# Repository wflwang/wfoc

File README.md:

# WFOC - 开源低成本高性能FOC电调

WFOC (WFL FOC) 是一款面向开源社区的低成本高性能无刷直流电机 FOC 控制器。项目参考 STM32 FOC 驱动、VESC 开源代码和 SimpleFOC，在国产 CIU32F003x5 (ARM Cortex-M0+) 上实现了完整的电机控制固件。

- 开源地址: https://github.com/wflwang/wfoc.git
- 邮箱: B5106D@Outlook.com

## 项目特点

- **低成本**: 采用国产 MCU (CIU32F003x5) 和 FD6288 栅极驱动，BOM 成本低
- **高性能**: 中断内全定点 Q16.16 运算（无浮点），20kHz PWM 电流环
- **双模式**: 同时支持 FOC 矢量控制和 BLDC 六步换相，可通过 `comm_mode` 配置切换
- **多观测器**: 滑模观测器 (SMO)、MXLEMMA 全阶观测器、MXV_Lambda 补偿、高频注入 (HFI)
- **VESC 风格协议**: 二进制 UART 协议，支持参数读写、实时遥测、高速流式打印
- **开源**: 硬件 (CERN-OHL-S v2) 和软件 (MIT) 全部开源

## 硬件架构

### 核心器件

| 器件 | 型号 | 封装 | 功能 |
|------|------|------|------|
| MCU | CIU32F003x5 | QFN-20 | 32位 ARM Cortex-M0+, 24MHz, 32KB Flash |
| 栅极驱动 | FD6288 | TSSOP-20 | 三相半桥驱动，内置自举二极管 |
| 运算放大器 | XOPA2333 | - | 2通道电流采样放大 |
| MOSFET | N-MOS | TO-252-2 | 3上 + 3下功率开关管 |

### 硬件特性

- **电源输入**: 10-48V DC
- **持续电流**: 20A（峰值 60A）
- **PWM 频率**: 8kHz-20kHz 可调（默认 20kHz）
- **电流采样**: 2路下桥臂电阻采样 (0.005R + 20x 运放)
- **通信接口**: UART (115200~921600) / PPM
- **保护功能**: 过流、过压、欠压、过温保护
- **调试接口**: SWD

### 引脚映射

引脚定义见 [board_config.h](software/config/board_config.h)，摘要：

| 功能 | 引脚 | 说明 |
|------|------|------|
| UART TX/RX | PC0 / PB5 | 串口通信 |
| PWM A 高/低 | PB2 / PB3 | A相上下管 |
| PWM B 高/低 | PC1 / PB7 | B相上下管 |
| PWM C 高/低 | PA1 / PA0 | C相上下管 |
| 电流采样 A/B | PB0 / PB1 | ADC CH0/CH1 |
| 相电压 U/V/W | PA3 / PA4 / PA5 | ADC CH3/CH4/CH5 |
| 母线电压 | PA7 | ADC CH7 |
| 温度 | PA6 | ADC CH6 |
| PPM 输入 | PB4 | TIM2 输入捕获 |

## 软件架构

### 目录结构

```
software/
├── main.c                  # 主程序入口（初始化与主循环）
├── interrupts.c            # 中断服务（ADC1 FOC环 / UART / PPM / SysTick）
├── Makefile                # 编译脚本
│
├── app/                    # 应用层
│   ├── app.c               # 状态机、安全监督、斜坡控制
│   ├── app_uart.c          # UART控制接口（VESC风格协议、实时遥测）
│   ├── app_ppm.c           # PPM脉冲解码
│   └── app_sound.c         # 电机发声
│
├── motor/                  # 电机控制核心
│   ├── mcpwm.c             # PWM后端桥接（duty/current/speed/position）
│   ├── observer.c          # 观测器（SMO / MXLEMMA / HFI + PLL）
│   ├── bldc.c              # BLDC六步换相（多种反电动势检测）
│   └── encoder.c           # 编码器接口
│
├── driver/mcu/             # MCU外设驱动
│   ├── adc.c               # ADC驱动（DMA多通道，偏置校准）
│   ├── pwm.c               # PWM驱动（TIM1三相中心对齐）
│   ├── uart.c              # UART驱动（环形缓冲收发）
│   ├── timer.c             # 定时器（PPM捕获/看门狗）
│   ├── gpio.c              # GPIO配置
│   ├── mcu_init.c          # 系统初始化（时钟/SysTick）
│   └── ciu32f003x.h        # MCU寄存器定义
│
├── conf/                   # 配置系统
│   ├── datatypes.h         # 核心数据类型（motor_state_t / mc_configuration_t）
│   ├── conf_default.c      # 默认参数
│   └── conf_general.c      # 配置管理（持久化接口）
│
├── config/                 # 编译时配置
│   ├── board_config.h      # 板级引脚映射与硬件参数
│   ├── hwconf.h            # 硬件目标选择（make HW=WFoc_V1）
│   └── fw_version.h        # 固件版本与功能开关
│
├── packet/                 # 通信协议
│   └── packet.c            # VESC风格帧封装（CRC16/CCITT）
│
├── startup/                # 启动文件
│   ├── linker.ld           # 链接脚本
│   └── startup_ciu32f003x.s# 启动汇编
│
└── util/                   # 工具库
    └── fixedpoint.c        # 定点数数学库（Q16.16, 三角函数, PI/PID, 陷波滤波）
```

### 数据流

```
ADC1 ISR (20kHz) ──► 电流采样 ──► Clarke ──► 观测器(角度/转速)
                                       │              │
                                       ▼              ▼
                                     Park ──► PI电流环 ──► 逆Park
                                                          │
                                                       SVPWM ──► TIM1 PWM
                                                          │
应用层 (main loop)                                        │
  app_process() ──► mcpwm_set_*() ──► foc_state.iq_set ───┘
  app_uart_process() ──► 遥测发送 ──► UART
```

### 核心功能实现状态

- [x] FOC 矢量控制（Clarke/Park/SVPWM/电流环PI）
- [x] BLDC 六步换相（ADC/比较器/过零检测 + 参数自学习）
- [x] 观测器（SMO / MXLEMMA / HFI + PLL 锁相环）
- [x] 定点数数学库（Q16.16，中断内无浮点）
- [x] VESC 风格 UART 协议（参数读写、固件版本、终端命令）
- [x] 实时遥测（3相电流、3相电压、转速、d/q轴等）
- [x] 高速流式打印（COMM_GET_VALUES_SELECTIVE + streaming）
- [x] ADC 偏置自校准（上电自动测量零电流偏移）
- [x] 安全监督（过流/过压/欠压/过温保护 + 故障状态机）
- [x] PPM 输入控制
- [x] 电机发声功能
- [ ] 速度闭环 PI（当前为前馈，参数已预留）
- [ ] 位置闭环控制
- [ ] 弱磁控制 / 过调制 / 陷波滤波（框架已建，待接入电流环）
- [ ] Flash 参数持久化（接口已定义，存储待实现）

## 编译环境

### 工具链安装

固件目标为 ARM Cortex-M0+，需要 `arm-none-eabi-gcc` 交叉编译工具链。

**Windows:**
1. 下载 [GNU Arm Embedded Toolchain](https://developer.arm.com/tools-and-software/open-source-software/developer-tools/gnu-toolchain/gnu-rm/downloads)
2. 解压并将 `bin` 目录加入系统 `PATH`
3. 安装 [Make for Windows](http://gnuwin32.sourceforge.net/packages/make.htm) 或使用 MSYS2

**Linux (Ubuntu/Debian):**
```bash
sudo apt install gcc-arm-none-eabi binutils-arm-none-eabi openocd
```

**macOS (Homebrew):**
```bash
brew install arm-gcc-bin openocd
```

### 验证工具链

```bash
arm-none-eabi-gcc --version    # 需要 10.x 或以上
arm-none-eabi-objcopy --version
openocd --version              # 烧录用
```

### 仿真环境（可选）

仿真在 PC 上运行，验证 FOC 定点算法，只需系统自带 GCC：

```bash
gcc --version    # Windows 可用 MinGW / MSYS2 的 gcc
```

## 编译步骤

### 编译固件

```bash
cd software
make              # 默认硬件目标 WFoc_V1
```

指定硬件目标与优化：
```bash
make HW=WFoc_V1   # 选择硬件版本（当前支持 V1）
make clean         # 清理构建产物
make size          # 查看 Flash/RAM 占用
make info          # 打印源文件列表和编译选项
```

编译成功后输出：
- `build/wfoc.elf` - ELF 可执行文件
- `build/wfoc.hex` - Intel HEX（烧录用）
- `build/wfoc.bin` - 二进制文件
- `build/wfoc.map` - 链接映射表

### 烧录固件

通过 ST-Link / J-Link + OpenOCD 烧录：
```bash
make flash        # 调用 openocd 烧录 build/wfoc.hex
```

也可手动烧录：
```bash
openocd -f interface/stlink.cfg -f target/ciu32f003x.cfg \
    -c "program build/wfoc.hex verify reset exit 0x08000000"
```

### 运行仿真

```bash
# Windows / Linux / macOS 均可
gcc -O2 -o simulation/sim_foc.exe simulation/sim_main.c software/util/fixedpoint.c -lm
./simulation/sim_foc.exe        # Linux/macOS
.\simulation\sim_foc.exe        # Windows PowerShell
```

仿真说明：
- 仿真使用**真实的定点数库** (`fixedpoint.c`)，与固件 ISR 完全相同的 Q16.16 运算
- `sim_main.c` 顶部 `SIM_USE_PERFECT_ANGLE` 开关：
  - `1` = 完美角度（验证 FOC 电流环本身），电机应加速到 400+ RPM
  - `0` = 观测器模式（验证 FOC + 观测器），验证角度估算

## 通信协议

### UART 接口

- 默认波特率: 115200（可通过参数调整为 921600 以支持高速打印）
- 格式: 8N1
- 协议: VESC 风格二进制帧

### 帧格式

```
短帧 (<256字节):  [0x02] [len] [payload...] [crc_hi] [crc_lo] [0x03]
长帧 (>=256字节): [0x03] [len_hi] [len_lo] [payload...] [crc_hi] [crc_lo] [0x03]
```
- `payload` = `[command] [data...]`
- CRC: CRC-16/CCITT (poly 0x1021, init 0xFFFF)

### 支持的命令

| 命令 | 名称 | 说明 |
|------|------|------|
| 0 | COMM_FW_VERSION | 获取固件版本与硬件名称 |
| 2 | COMM_GET_VALUES | 获取完整实时数据（含3相电流/电压/转速） |
| 4 | COMM_SET_DUTY | 设置占空比 (x1e5) |
| 5 | COMM_SET_CURRENT | 设置电流 (x1e3) |
| 6 | COMM_SET_CURRENT_BRAKE | 制动电流 (x1e3) |
| 7 | COMM_SET_RPM | 设置转速 ERPM |
| 8 | COMM_SET_POS | 设置位置 (x1e6) |
| 11 | COMM_GET_MCCONF | 读取电机配置 |
| 12 | COMM_SET_MCCONF | 写入电机配置 |
| 13/14 | COMM_GET/SET_APPCONF | 读取/写入应用配置 |
| 15 | COMM_DETECT_MOTOR_PARAM | 电机参数检测 |
| 17 | COMM_TERMINAL_CMD | 终端命令 (help/stop/restart/alive) |
| 18 | COMM_GET_VALUES_SELECTIVE | 高速选择性遥测（见下） |

### 实时遥测与高速打印

**完整遥测 (COMM_GET_VALUES)**：请求一次返回一帧，包含温度、3相电流、3相电压、d/q轴、占空比、转速、位置、母线电压、功率、故障码等。

**高速选择性遥测 (COMM_GET_VALUES_SELECTIVE)**：

上位机发送 `[mask:u32][rate_ms:u16]`，固件按位掩码只打包需要的字段，大幅减小数据包。`rate_ms > 0` 时开启**主动流式发送**（streaming），固件在主循环按设定间隔自动发送，无需反复请求。

字段掩码位定义（见 [datatypes.h](software/conf/datatypes.h)）：
```
bit 0-2:   IA / IB / IC     (3相电流)
bit 3-5:   VA / VB / VC     (3相电压)
bit 6-9:   ID / IQ / VD / VQ (d/q轴电流电压)
bit 10:    DUTY
bit 11:    SPEED (ERPM)
bit 12:    POSITION (rad)
bit 13:    VBUS
bit 14-15: TEMP_MOS / TEMP_MOT
bit 16:    POWER
```

示例：以 1ms 速率只打印 3相电流 + 3相电压 + 转速：
```
mask = IA|IB|IC|VA|VB|VC|SPEED = 0x208F
发送: COMM_GET_VALUES_SELECTIVE + [0x8F,0x20,0x00,0x00] + [0x01,0x00]
```

**实现原理**（高速打印关键）：
1. ADC 中断 (20kHz) 只采集数据存入 `motor_state` 变量，**不在中断中发串口**
2. 主循环中一次性组装数据包通过 UART 发送
3. streaming 模式避免请求-响应往返延迟
4. 提高波特率 (921600) 可进一步缩短发送时间

## 配置与调参

所有电机参数可通过 UART 在线调整（COMM_GET/SET_MCCONF），参数定义见 [datatypes.h](software/conf/datatypes.h) 的 `mc_configuration_t`，默认值见 [conf_default.c](software/conf/conf_default.c)。

关键参数：
- `comm_mode`: 0=FOC, 1=BLDC
- `observer_type`: 0=无, 1=SMO, 2=MXLEMMA, 3=MXV_Lambda, 4=HFI
- `motor_r / motor_l / motor_flux_linkage / motor_poles`: 电机参数
- `foc_current_kp / ki`: 电流环 PI 增益
- `foc_speed_kp / ki`: 速度环 PI 增益
- `l_max_current / l_max_speed / l_max_duty`: 限幅

## 贡献指南

欢迎任何形式的贡献！请遵循以下步骤：

1. Fork 本仓库
2. 创建功能分支 (`git checkout -b feature/your-feature`)
3. 提交代码 (`git commit -am 'Add some feature'`)
4. 推送到分支 (`git push origin feature/your-feature`)
5. 创建 Pull Request

## 许可证

本项目采用双重许可证：

| 部分 | 许可证 | 文件 |
|------|--------|------|
| 软件代码 | MIT License | [LICENSE](LICENSE) |
| 硬件设计文件 | CERN-OHL-S v2 | [LICENSE-HARDWARE](LICENSE-HARDWARE) |

## 致谢

感谢以下开源项目的启发和参考：

- [VESC](https://github.com/vedderb/bldc) - BLDC 开源电调
- [SimpleFOC](https://github.com/simplefoc/Arduino-FOC) - 简易 FOC 库

## 联系方式

- 邮箱: B5106D@Outlook.com
- GitHub Issues: [提交 Issue](https://github.com/wflwang/wfoc/issues)

---

**免责声明**: 本项目仅供学习和研究使用。使用本项目造成的任何损失，作者不承担责任。请在使用前充分测试并确保安全。

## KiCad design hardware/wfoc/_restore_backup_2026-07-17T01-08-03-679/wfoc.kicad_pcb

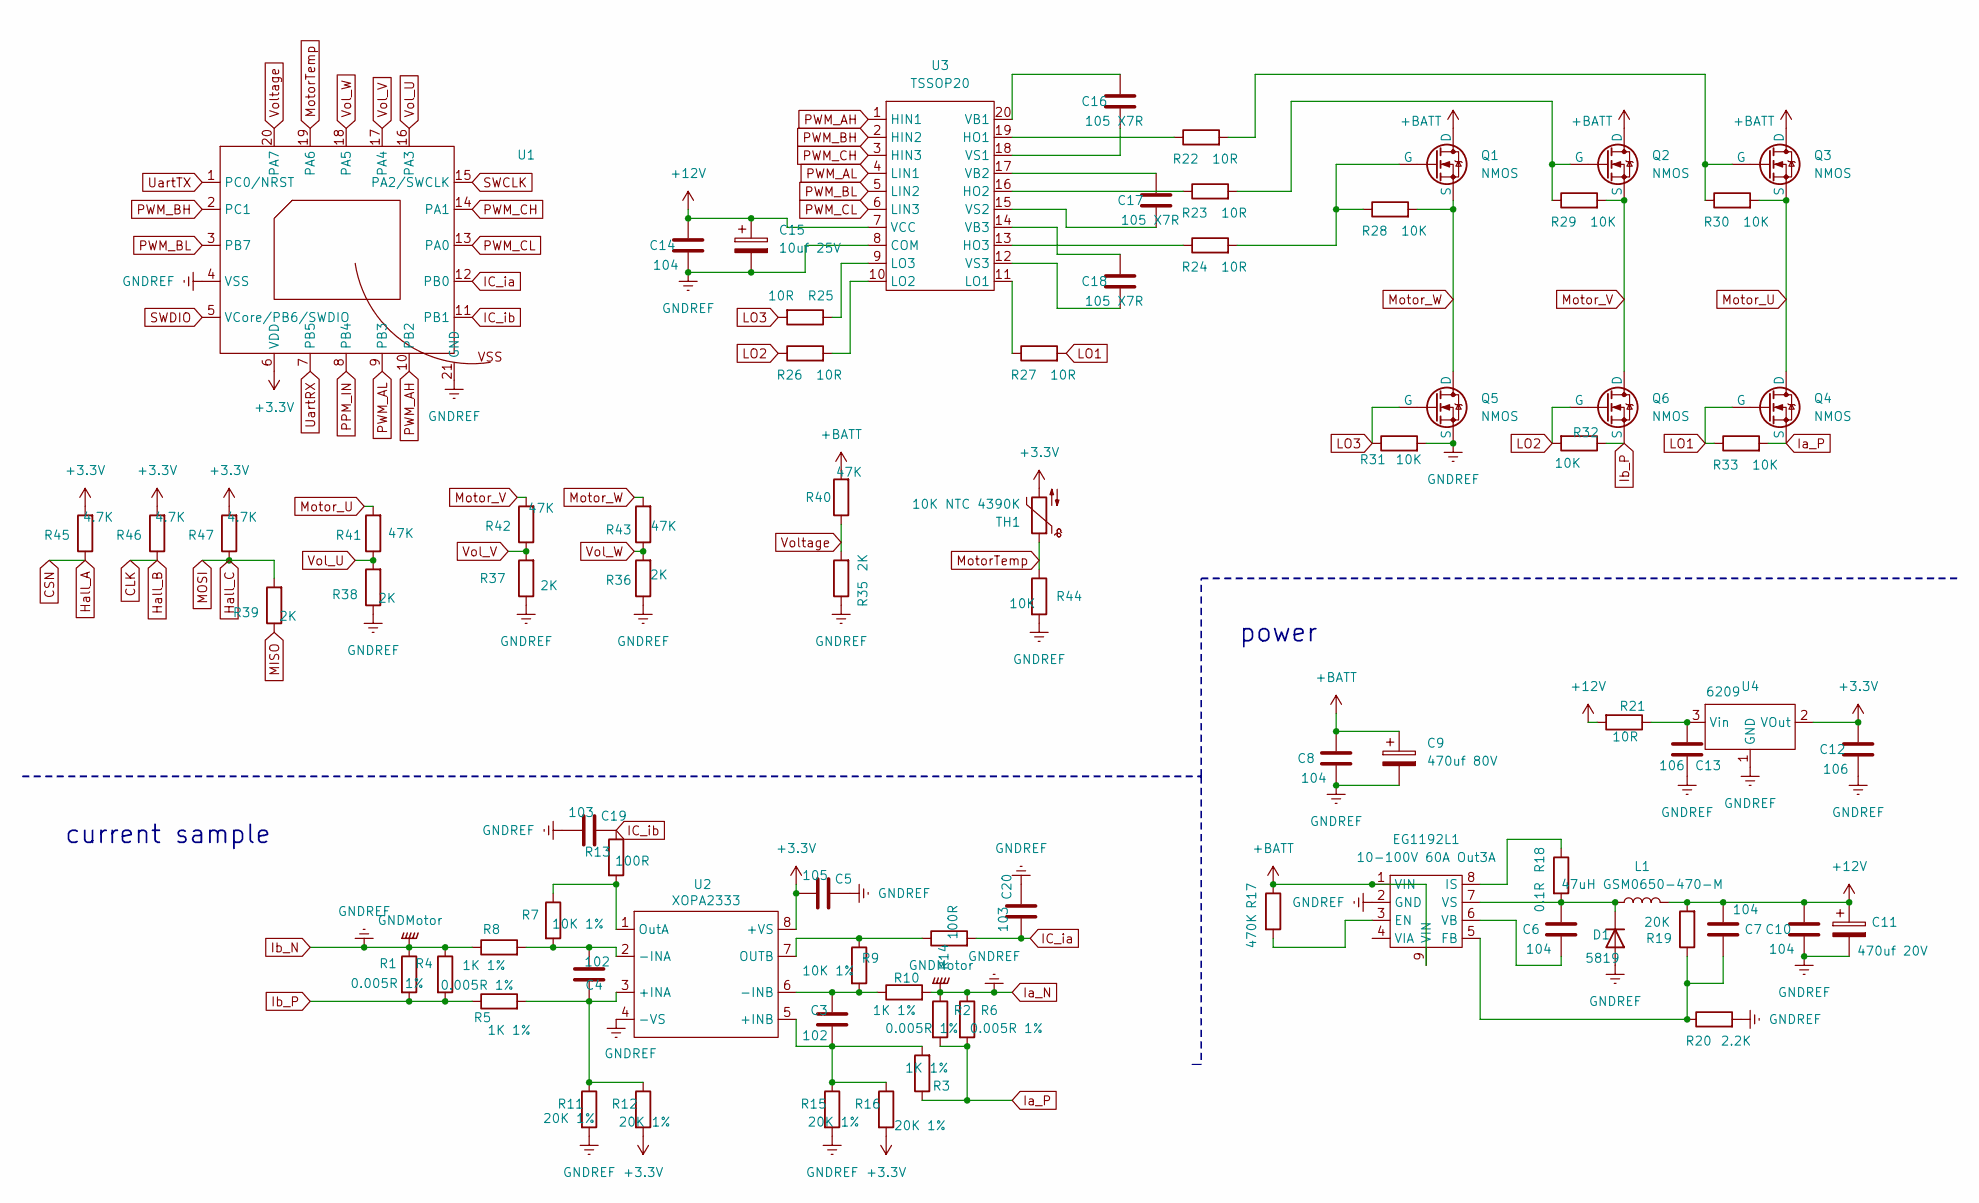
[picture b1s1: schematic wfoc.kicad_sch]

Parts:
C3, C4: 102; C_0603_1608Metric
C5: 105; C_0603_1608Metric
C6, C7, C8, C10, C14: 104; C_0603_1608Metric
C9: 470uf 80V; CP_Radial_D10.0mm_P7.50mm
C11: 470uf 20V; CP_Radial_D10.0mm_P7.50mm
C12, C13: 106; C_0805_2012Metric
C15: 10uf 25V; C_0603_1608Metric
C16, C17, C18: 105 X7R; C_0603_1608Metric
C19, C20: 103; C_0603_1608Metric
D1: 5819; D_1206_3216Metric_Pad1.42x1.75mm_HandSolder
EG1192L1: 10-100V 60A Out3A; SOP-8-1EP_6.0x4.9mm_P1.27mm_EP2.4x3.3mm
L1: 47uH GSM0650-470-M; L_7.5x6.6mm
Q1, Q2, Q3, Q4, Q5, Q6: NMOS; TO-252-2
R1, R2, R4, R6: 0.005R 1%; R_2512_6332Metric
R3, R5, R8, R10: 1K 1%; R_0603_1608Metric
R7, R9: 10K 1%; R_0603_1608Metric
R11, R12, R15, R16: 20K 1%; R_0603_1608Metric
R13, R14: 100R; R_0603_1608Metric
R17: 470K; R_0603_1608Metric
R18: 0.1R; R_1206_3216Metric
R19: 20K; R_0603_1608Metric
R20: 2.2K; R_0603_1608Metric
R21, R22, R23, R24, R25, R26, R27: 10R; R_0603_1608Metric
R28, R29, R30, R31, R32, R33: 10K; R_0603_1608Metric
R35: 2K; R_0603_1608Metric
R36, R37, R38, R39: 2K; R_0402_1005Metric
R40: 47K; R_0805_2012Metric
R41, R42, R43: 47K; R_0603_1608Metric
R44: 10K; R_0402_1005Metric
R45, R46, R47: 4.7K; R_0603_1608Metric
TH1: 10K NTC 4390K; R_0603_1608Metric
U1: QFN-20-1EP_3x3mm_P0.4mm_EP1.5x1.5mm
U2: XOPA2333; SOP-8_3.9x4.9mm_P1.27mm
U3: TSSOP20; TSSOP-20_4.4x6.5mm_P0.65mm
U4: 6209; SOT-23

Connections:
+3.3V: C5.1, C12.2, R12.2, R16.2, R45.2, R46.2, R47.2, TH1.2, U1.6 (VDD), U2.8 (+VS), U4.2 (VOut)
+12V: C7.1, C10.2, C11.1, C14.2, C15.1, L1.2, R19.2, R21.2, U3.7 (VCC)
+BATT: C8.2, C9.1, EG1192L1.1 (VIN), EG1192L1.9 (VIN), Q1.2 (D), Q2.2 (D), Q3.2 (D), R17.1, R40.2; also elsewhere on the board
IC_ia: C20.1, R14.2, U1.12 (PB0)
IC_ib: C19.2, R13.1, U1.11 (PB1)
Ia_N: C5.2, C8.1, C9.2, C10.1, C11.2, C12.1, C13.1, C14.1, C15.2, C19.1, C20.2, D1.2 (A), EG1192L1.2 (GND), Q5.3 (S), R1.1, R2.1, R4.1, R6.1, R8.1, R10.2, R11.2, R15.2, R20.2, R31.2, R35.1, R36.1, R37.1, R38.1, R44.2, U1.4 (VSS), U1.21 (GND), U2.4 (-VS), U3.8 (COM), U4.1 (GND); also elsewhere on the board
Ia_P: Q4.3 (S), R2.2, R3.1, R6.2, R33.2
Ib_P: Q6.3 (S), R1.2, R4.2, R5.1, R32.1
LO1: Q4.1 (G), R27.2, R33.1
LO2: Q6.1 (G), R26.1, R32.2
LO3: Q5.1 (G), R25.2, R31.1
MotorTemp: R44.1, TH1.1, U1.19 (PA6)
Motor_U: Q3.3 (S), Q4.2 (D), R30.2, R41.2
Motor_V: Q2.3 (S), Q6.2 (D), R29.2, R42.2
Motor_W: Q1.3 (S), Q5.2 (D), R28.2, R43.2
unnamed: C6.2, D1.1 (K), EG1192L1.7 (VS), L1.1, R18.2
unnamed: EG1192L1.3 (EN), R17.2
unnamed: C7.2, EG1192L1.5 (FB), R19.1, R20.1
unnamed: EG1192L1.8 (IS), R18.1
unnamed: C6.1, EG1192L1.6 (VB)
unnamed: Q1.1 (G), R24.2, R28.1
unnamed: Q2.1 (G), R23.2, R29.1
unnamed: Q3.1 (G), R22.2, R30.1
unnamed: C4.2, R5.2, R11.1, R12.1, U2.3 (+INA)
unnamed: C3.2, R3.2, R15.1, R16.1, U2.5 (+INB)
unnamed: C4.1, R7.2, R8.2, U2.2 (-INA)
unnamed: C3.1, R9.2, R10.1, U2.6 (-INB)
unnamed: R9.1, R14.1, U2.7 (OUTB)
unnamed: R7.1, R13.2, U2.1 (OutA)
unnamed: R22.1, U3.19 (HO1)
unnamed: R23.1, U3.16 (HO2)
unnamed: R24.1, U3.13 (HO3)
unnamed: R27.1, U3.11 (LO1)
unnamed: R26.2, U3.10 (LO2)
unnamed: R25.1, U3.9 (LO3)
unnamed: C16.2, U3.20 (VB1)
unnamed: C17.2, U3.17 (VB2)
unnamed: C18.2, U3.14 (VB3)
unnamed: C16.1, U3.18 (VS1)
unnamed: C17.1, U3.15 (VS2)
unnamed: C18.1, U3.12 (VS3)
unnamed: C13.2, R21.1, U4.3 (Vin)
PPM_IN: U1.8 (PB4)
PWM_AH: U1.10 (PB2), U3.1 (HIN1)
PWM_AL: U1.9 (PB3), U3.4 (LIN1)
PWM_BH: U1.2 (PC1), U3.2 (HIN2)
PWM_BL: U1.3 (PB7), U3.5 (LIN2)
PWM_CH: U1.14 (PA1), U3.3 (HIN3)
PWM_CL: U1.13 (PA0), U3.6 (LIN3)
SWCLK: U1.15 (PA2/SWCLK)
SWDIO: U1.5 (VCore/PB6/SWDIO)
UartRX: U1.7 (PB5)
UartTX: U1.1 (PC0/NRST)
Voltage: R35.2, R40.1, U1.20 (PA7); also elsewhere on the board

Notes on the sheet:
current sample
power

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
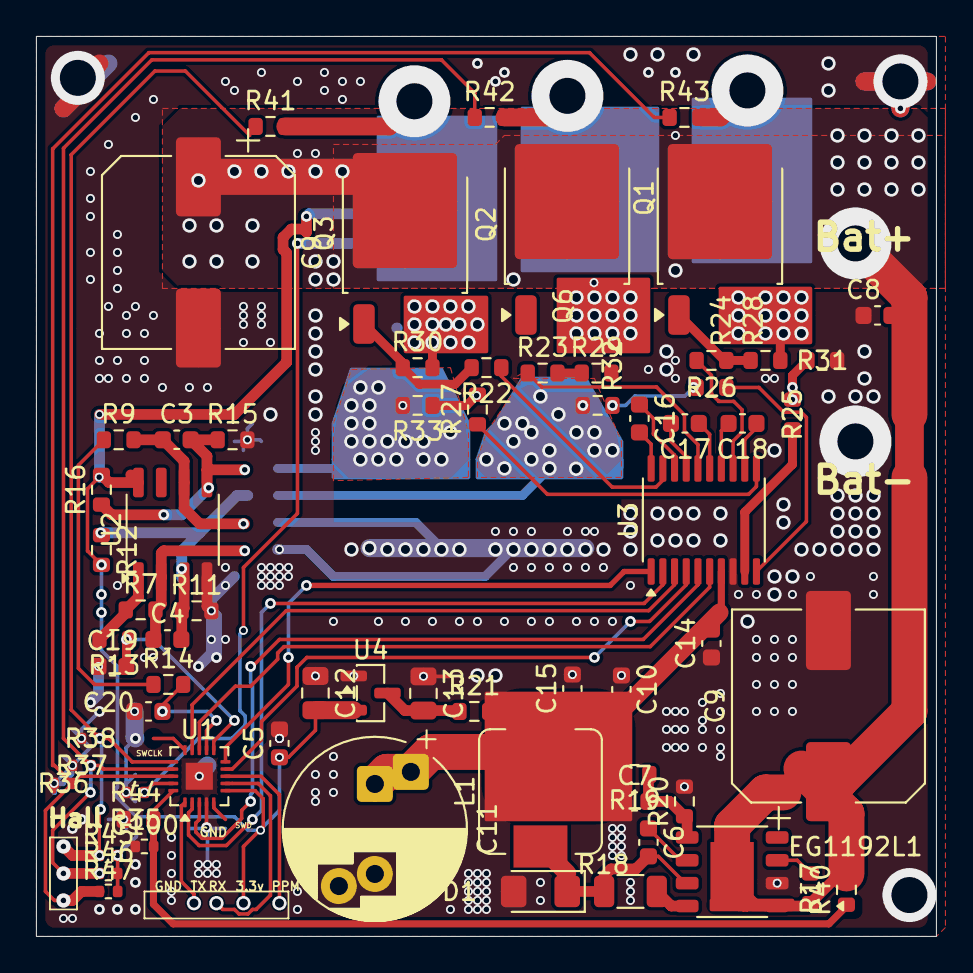
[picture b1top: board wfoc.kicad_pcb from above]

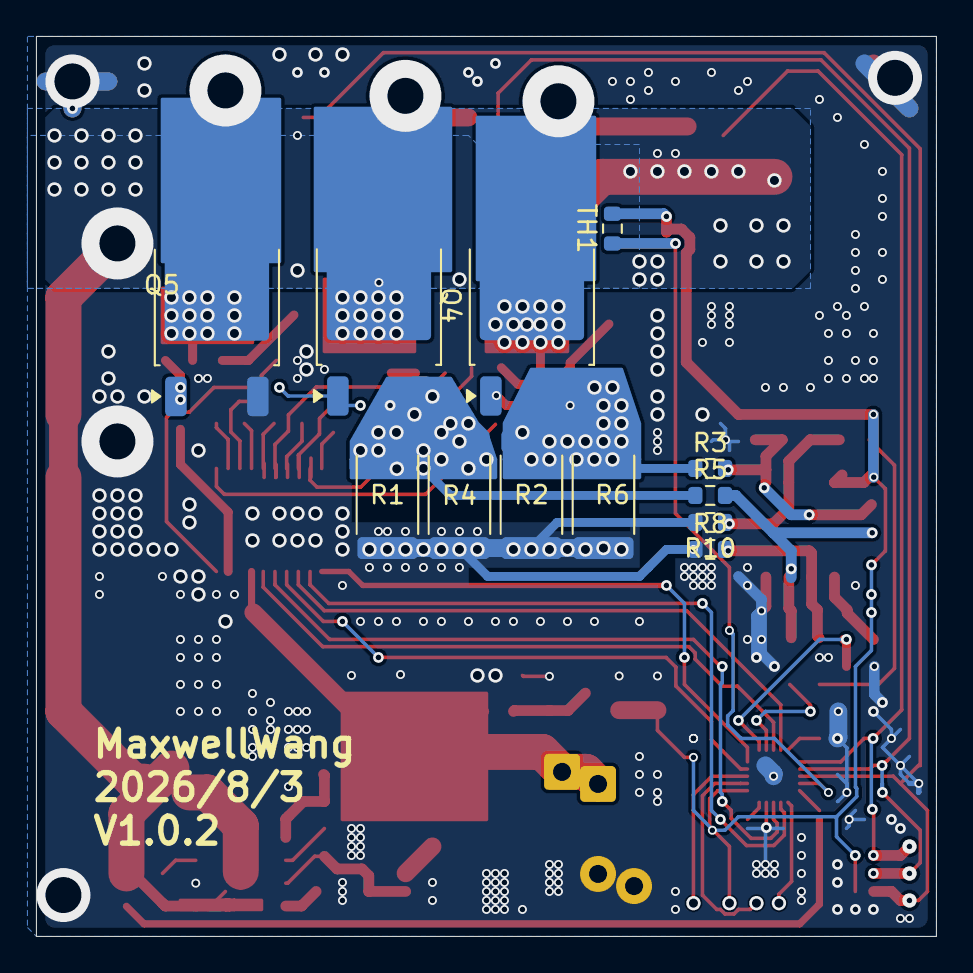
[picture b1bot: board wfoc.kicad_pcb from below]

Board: 2 copper layers, 50.0 x 50.0 mm, 79 parts (12 on the bottom side), 52 nets.

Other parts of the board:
C9#2: 470uf 80V; CP_Elec_10x12.5
C100: 104; R_0402_1005Metric

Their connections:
+BATT: C9#2.1; also elsewhere on the board
Ia_N: C9#2.2, C100.1; also elsewhere on the board
Voltage: C100.2; also elsewhere on the board

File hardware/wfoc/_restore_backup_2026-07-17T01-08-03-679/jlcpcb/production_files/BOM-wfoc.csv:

Comment,Designator,Footprint,LCSC,Quantity
NMOS,Q1,TO-252-2,,1
105,C5,C_0603_1608Metric,,1
10R,R23,R_0603_1608Metric,,1
100R,R13,R_0603_1608Metric,,1
NMOS,Q3,TO-252-2,,1
10K,R32,R_0603_1608Metric,,1
10K,R29,R_0603_1608Metric,,1
NMOS,Q2,TO-252-2,,1
10R,R24,R_0603_1608Metric,,1
10K,R28,R_0603_1608Metric,,1
10K,R30,R_0603_1608Metric,,1
20K 1%,R15,R_0603_1608Metric,,1
104,C7,C_0603_1608Metric,,1
2.2K,R20,R_0603_1608Metric,,1
103,C19,C_0603_1608Metric,,1
10R,R27,R_0603_1608Metric,,1
10K 1%,R9,R_0603_1608Metric,,1
10K,R44,R_0402_1005Metric,,1
2K,R38,R_0402_1005Metric,,1
0.1R,R18,R_1206_3216Metric,,1
10R,R25,R_0603_1608Metric,,1
104,C14,C_0603_1608Metric,,1
105 X7R,C17,C_0603_1608Metric,,1
4.7K,R47,R_0402_1005Metric,,1
47K,R40,R_0805_2012Metric,,1
4.7K,R45,R_0402_1005Metric,,1
10K,R33,R_0603_1608Metric,,1
10K,R31,R_0603_1608Metric,,1
20K 1%,R11,R_0603_1608Metric,,1
47uH GSM0650-470-M,L1,L_7.5x6.6mm,,1
470K,R17,R_0603_1608Metric,,1
47K,R42,R_0603_1608Metric,,1
104,C6,C_0603_1608Metric,,1
106,C12,C_0805_2012Metric,,1
20K 1%,R16,R_0603_1608Metric,,1
10R,R26,R_0603_1608Metric,,1
10R,R22,R_0603_1608Metric,,1
470uf 80V,C9,CP_Elec_10x12.5,,1
2K,R36,R_0402_1005Metric,,1
104,C10,C_0603_1608Metric,,1
100R,R14,R_0603_1608Metric,,1
20K 1%,R12,R_0603_1608Metric,,1
5819,D1,D_1206_3216Metric_Pad1.42x1.75mm_HandSolder,,1
TSSOP20,U3,TSSOP-20_4.4x6.5mm_P0.65mm,,1
2K,R37,R_0402_1005Metric,,1
102,C4,C_0603_1608Metric,,1
20K,R19,R_0603_1608Metric,,1
47K,R41,R_0603_1608Metric,,1
102,C3,C_0603_1608Metric,,1
105 X7R,C16,C_0603_1608Metric,,1
47K,R43,R_0603_1608Metric,,1
103,C20,C_0603_1608Metric,,1
470uf 20V,C11,CP_Radial_D10.0mm_P5.00mm_P7.50mm,,1
10R,R21,R_0603_1608Metric,,1
2K,R35,R_0603_1608Metric,,1
XOPA2333,U2,SOP-8_3.9x4.9mm_P1.27mm,,1
10K 1%,R7,R_0603_1608Metric,,1
106,C13,C_0805_2012Metric,,1
~,U1,QFN-20-1EP_3x3mm_P0.4mm_EP1.5x1.5mm,,1
104,C8,C_0603_1608Metric,,1
6209,U4,SOT-23,,1
105 X7R,C18,C_0603_1608Metric,,1
4.7K,R46,R_0402_1005Metric,,1
10uf 25V,C15,C_0603_1608Metric,,1
10K NTC 4390K,TH1,R_0603_1608Metric,,1
NMOS,Q5,TO-252-2,,1
0.005R 1%,,R_2512_6332Metric,,0
0.005R 1%,,R_2512_6332Metric,,0
NMOS,Q6,TO-252-2,,1
1K 1%,R10,R_0603_1608Metric,,1
1K 1%,R5,R_0603_1608Metric,,1
1K 1%,R8,R_0603_1608Metric,,1
NMOS,Q4,TO-252-2,,1
1K 1%,R3,R_0603_1608Metric,,1
0.005R 1%,,R_2512_6332Metric,,0
0.005R 1%,,R_2512_6332Metric,,0

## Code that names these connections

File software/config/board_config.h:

/*
 * board_config.h - WFOC V1 Board Pin Mapping
 *
 * Hardware: CIU32F003x5 (QFN-20, ARM Cortex-M0+)
 * Gate Driver: FD6288 (TSSOP-20, 3-phase half-bridge)
 * Current Sense: 0.005R shunt + XOPA2333 op-amp (2 channels)
 *
 * WFOC (WFL FOC) - Open Source Low-Cost High-Performance FOC Controller
 * Copyright (c) 2026 wflwang
 * Licensed under MIT License
 */

#ifndef BOARD_CONFIG_H
#define BOARD_CONFIG_H

/* ======================================================================== */
/* MCU Clock Configuration                                                   */
/* ======================================================================== */
#define MCU_CLK_HZ          24000000   /* 24 MHz internal RC */
#define ADC_CLK_HZ          12000000   /* ADC clock */
#define PWM_FREQ_HZ         20000      /* Default PWM frequency */
#define PWM_FREQ_MIN_HZ     8000       /* Min PWM frequency */
#define PWM_FREQ_MAX_HZ     20000      /* Max PWM frequency */

/* ======================================================================== */
/* Pin Definitions - from PCB net mapping                                   */
/* ======================================================================== */

/* --- UART --- */
#define UART_TX_PORT        GPIOC
#define UART_TX_PIN         0           /* PC0 (pin 1, shared with NRST) */
#define UART_RX_PORT        GPIOB
#define UART_RX_PIN         5           /* PB5 (pin 7) */
#define UART_BAUDRATE       115200

/* --- PWM (FD6288 Gate Driver) --- */
/* Phase A */
#define PWM_AH_PORT         GPIOB
#define PWM_AH_PIN          2           /* PB2 (pin 10) - A high */
#define PWM_AL_PORT         GPIOB
#define PWM_AL_PIN          3           /* PB3 (pin 9) - A low */

/* Phase B */
#define PWM_BH_PORT         GPIOC
#define PWM_BH_PIN          1           /* PC1 (pin 2) - B high */
#define PWM_BL_PORT         GPIOB
#define PWM_BL_PIN          7           /* PB7 (pin 3) - B low */

/* Phase C */
#define PWM_CH_PORT         GPIOA
#define PWM_CH_PIN          1           /* PA1 (pin 14) - C high */
#define PWM_CL_PORT         GPIOA
#define PWM_CL_PIN          0           /* PA0 (pin 13) - C low */

/* --- ADC Channels --- */
/* Current sensing (2 channels, phase A & B) */
#define ADC_IA_CHANNEL      ADC_CH0     /* PB0 (pin 12) - Phase A current */
#define ADC_IA_PORT         GPIOB
#define ADC_IA_PIN          0

#define ADC_IB_CHANNEL      ADC_CH1     /* PB1 (pin 11) - Phase B current */
#define ADC_IB_PORT         GPIOB
#define ADC_IB_PIN          1

/* Phase voltage sensing */
#define ADC_VOL_U_CHANNEL   ADC_CH3     /* PA3 (pin 16) - Phase U voltage */
#define ADC_VOL_V_CHANNEL   ADC_CH4     /* PA4 (pin 17) - Phase V voltage */
#define ADC_VOL_W_CHANNEL   ADC_CH5     /* PA5 (pin 18) - Phase W voltage */

/* Bus voltage sensing */
#define ADC_VBUS_CHANNEL    ADC_CH7     /* PA7 (pin 20) - Bus voltage */

/* Temperature sensing */
#define ADC_TEMP_CHANNEL    ADC_CH6     /* PA6 (pin 19) - Motor temperature */

/* --- PPM Input --- */
#define PPM_PORT            GPIOB
#define PPM_PIN             4           /* PB4 (pin 8) */
#define PPM_TIMER           TIM2

/* --- SPI (reserved for remote control / OTA) ---
 * Note: MISO is connected to MOSI externally for half-duplex */
#define SPI_SCK_PORT        GPIOA
#define SPI_SCK_PIN         2           /* PA2 (shared with SWCLK) */
#define SPI_MOSI_PORT       GPIOA
#define SPI_MOSI_PIN        3           /* PA3 */
#define SPI_MISO_PORT       GPIOA
#define SPI_MISO_PIN        4           /* PA4 (not used internally) */
#define SPI_CSN_PORT        GPIOA
#define SPI_CSN_PIN         5           /* PA5 (chip select, active low) */

/* --- SWD Debug --- */
#define SWDIO_PORT          GPIOB
#define SWDIO_PIN           6           /* PB6 (pin 5) */
#define SWCLK_PORT          GPIOA
#define SWCLK_PIN           2           /* PA2 (pin 15) - shared with SPI_SCK */

/* ======================================================================== */
/* Hardware Parameters                                                       */
/* ======================================================================== */

/* Power supply */
#define VBUS_MIN_V          10.0f       /* Min bus voltage */
#define VBUS_MAX_V          48.0f       /* Max bus voltage */
#define VBUS_WARN_V         50.0f       /* Over-voltage warning */

/* Current sensing */
#define SHUNT_RESISTOR      0.005f      /* 5mΩ shunt resistor */
#define OP_AMP_GAIN         20.0f       /* Op-amp gain (adjustable via R5/R8) */
#define CURRENT_MAX_A       60.0f       /* Max measurable current */
#define CURRENT_CONT_A      20.0f       /* Continuous current rating */

/* ADC reference */
#define ADC_VREF_V          3.3f        /* ADC reference voltage */
#define ADC_RESOLUTION      4096        /* 12-bit ADC */
#define ADC_VREF_INT        3300        /* mV for fixed-point calc */

/* Voltage divider for bus voltage measurement */
/* VBUS -> R_top -> ADC -> R_bot -> GND */
#define VBUS_DIV_R_TOP      20000.0f    /* 20KΩ */
#define VBUS_DIV_R_BOT      2000.0f     /* 2KΩ */
#define VBUS_DIV_RATIO      ((VBUS_DIV_R_TOP + VBUS_DIV_R_BOT) / VBUS_DIV_R_BOT)

/* Temperature sensing (NTC) */
#define NTC_BETA            3950.0f     /* NTC B-value */
#define NTC_R25             10000.0f    /* NTC resistance at 25°C */
#define NTC_R_DIVIDER       10000.0f    /* Divider resistor */

/* MOSFET dead time (ns) */
#define DEADTIME_NS         500         /* 500ns default dead time */

/* PWM timer configuration */
#define PWM_TIMER           TIM1        /* Advanced timer for PWM */
#define PWM_PERIOD_DEFAULT  (MCU_CLK_HZ / (2 * PWM_FREQ_HZ))

/* ======================================================================== */
/* LED / Status (if available)                                              */
/* ======================================================================== */
/* No dedicated LED pin on this board - use UART for status */

#endif /* BOARD_CONFIG_H */
